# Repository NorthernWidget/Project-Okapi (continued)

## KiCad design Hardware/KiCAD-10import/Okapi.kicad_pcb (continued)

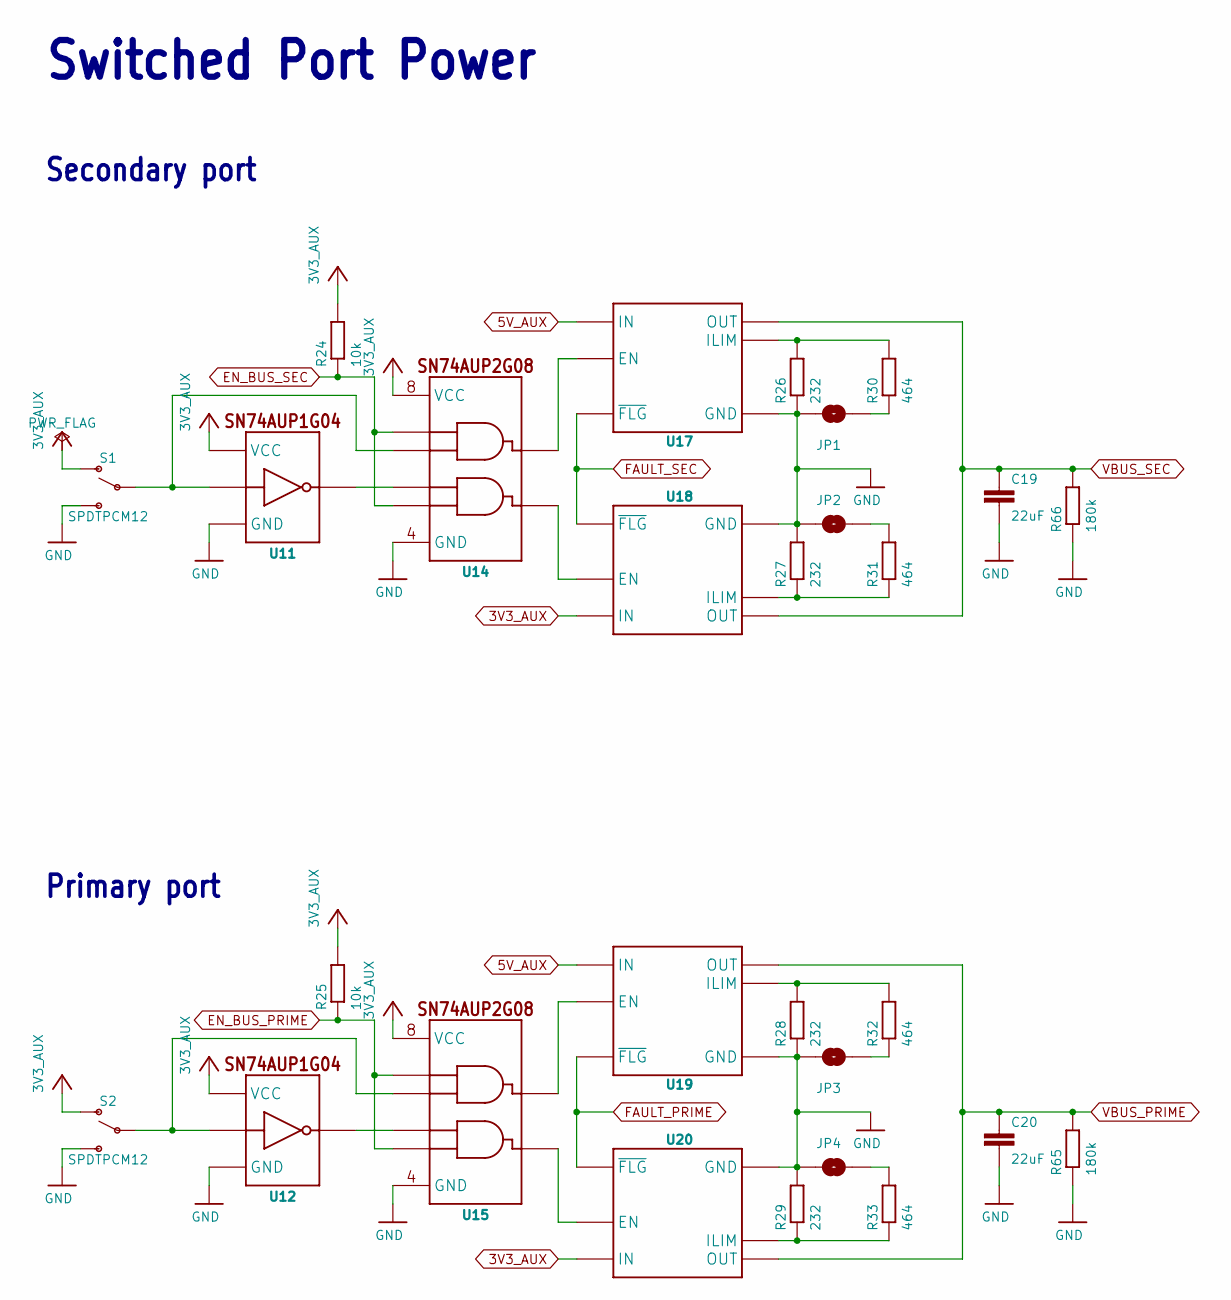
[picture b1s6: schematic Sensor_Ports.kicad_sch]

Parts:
C19, C20: 22uF; C0805; MPN GRM219R61C226ME15L; DIGIKEY 490-9952-1-ND
JP1, JP2, JP3, JP4: JUMPER-SMT_2_NO_SILK; SMT-JUMPER_2_NO_SILK
R24, R25: 10k; R0402; MPN RC0402FR-0710KL; DIGIKEY 311-10.0KLRCT-ND
R26, R27, R28, R29: 232; R0402; MPN RC0402FR-07232RL; DIGIKEY YAG3063CT-ND
R30, R31, R32, R33: 464; R0402; MPN RC0402FR-07464RL; DIGIKEY 311-464LRCT-ND
R65, R66: 180k; R0402; MPN RC0402FR-07180KL; DIGIKEY 311-180KLRCT-ND
S1, S2: SPDTPCM12; PCM12; MPN PCM12SMTR; DIGIKEY 401-2016-1-ND
U11, U12: SN74AUP1G04YFP; DSBGD_4; MPN SN74AUP1G04YFPR; DIGIKEY 296-25196-1-ND
U14, U15: SN74AUP2G08DQE; DQE_R-PX2SON-N8; MPN SN74AUP2G08DQER; DIGIKEY 296-25638-1-ND
U17, U18, U19, U20: MIC2544MSOP; MSOP_8; MPN MIC2544-1YMM; DIGIKEY 576-1738-5-ND

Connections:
3V3_AUX: R24.2, R25.2, S1.1 (O), S2.1 (O), U11.A2 (VCC), U12.A2 (VCC), U14.8 (VCC), U15.8 (VCC), U18.7 (IN), U20.7 (IN); also elsewhere on the board
5V_AUX: U17.7 (IN), U19.7 (IN); also elsewhere on the board
EN_BUS_PRIME: R25.1, U15.1 (A1), U15.6 (B2); also elsewhere on the board
EN_BUS_SEC: R24.1, U14.1 (A1), U14.6 (B2); also elsewhere on the board
FAULT_PRIME: U19.2 (~FLG), U20.2 (~FLG); also elsewhere on the board
FAULT_SEC: U17.2 (~FLG), U18.2 (~FLG); also elsewhere on the board
GND: C19.2, C20.2, JP1.1, JP2.1, JP3.1, JP4.1, R26.1, R27.2, R28.1, R29.2, R65.1, R66.1, S1.3 (S), S2.3 (S), U11.B1 (GND), U12.B1 (GND), U14.4 (GND), U15.4 (GND), U17.3 (GND), U18.3 (GND), U19.3 (GND), U20.3 (GND); also elsewhere on the board
unnamed: JP1.2, R30.1
unnamed: JP2.2, R31.2
unnamed: JP3.2, R32.1
unnamed: JP4.2, R33.2
unnamed: S1.2, U11.A1 (A), U14.2 (B1)
unnamed: S2.2, U12.A1 (A), U15.2 (B1)
unnamed: U11.B2 (Y), U14.5 (A2)
unnamed: U12.B2 (Y), U15.5 (A2)
unnamed: U14.7 (Y1), U17.1 (EN)
unnamed: U14.3 (Y2), U18.1 (EN)
unnamed: U15.7 (Y1), U19.1 (EN)
unnamed: U15.3 (Y2), U20.1 (EN)
unnamed: R26.2, R30.2, U17.5 (ILIM)
unnamed: R27.1, R31.1, U18.5 (ILIM)
unnamed: R28.2, R32.2, U19.5 (ILIM)
unnamed: R29.1, R33.1, U20.5 (ILIM)
VBUS_PRIME: C20.1, R65.2, U19.6 (OUT), U19.8 (OUT), U20.6 (OUT), U20.8 (OUT); also elsewhere on the board
VBUS_SEC: C19.1, R66.2, U17.6 (OUT), U17.8 (OUT), U18.6 (OUT), U18.8 (OUT); also elsewhere on the board

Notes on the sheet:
Primary port
Secondary port
Switched Port Power

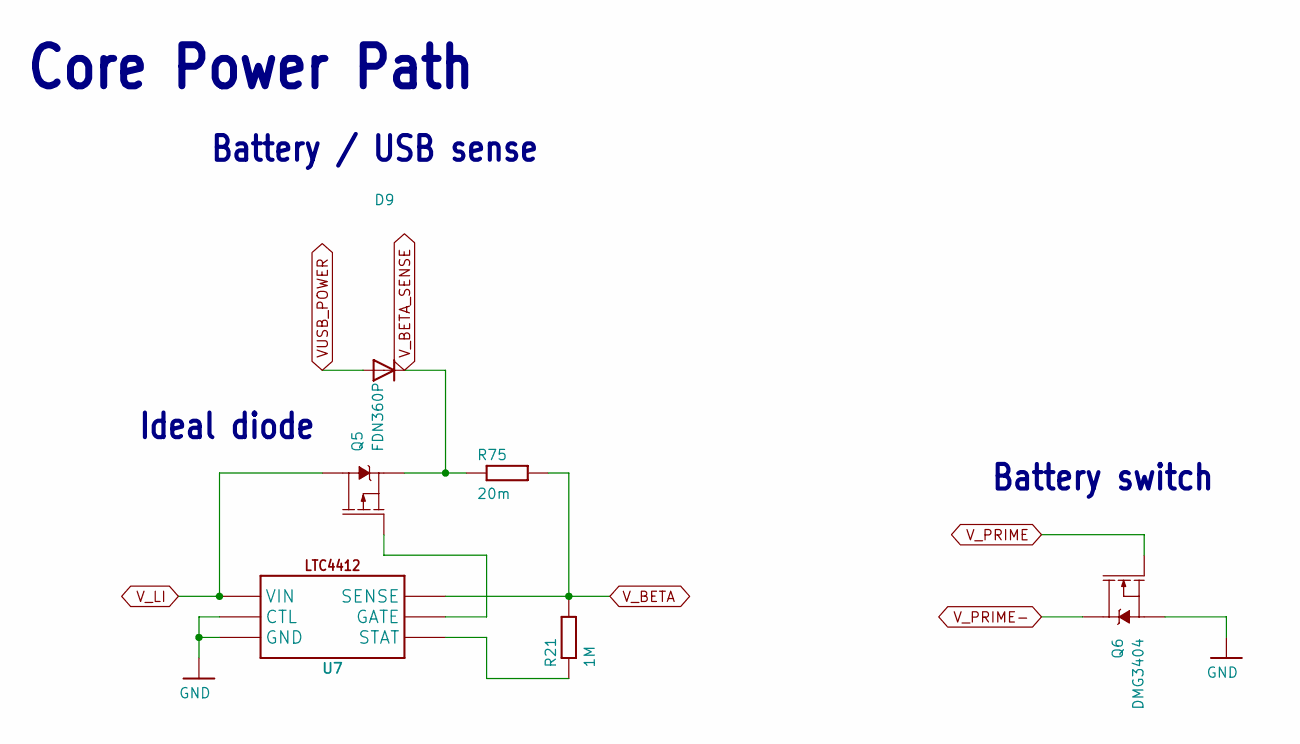
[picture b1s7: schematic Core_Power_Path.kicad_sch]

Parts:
D9: DIODEDO-214AC; DO214AC; MPN B340A-13-F; DIGIKEY B340A-FDICT-ND
Q5: FDN360P; SOT23-3; MPN FDN360P; DIGIKEY FDN360PCT-ND
Q6: DMG3404; SOT23-3; MPN DMG3404L-7; DIGIKEY DMG3404L-7DICT-ND
R21: 1M; R0603; MPN ERJ-3EKF1004V; DIGIKEY P1.00MHCT-ND
R75: 20m; R0805; MPN ERJ-6BWFR020V; DIGIKEY P.02AQCT-ND
U7: LTC4412S6; SOT23-6L; MPN LTC4412ES6#TRPBF; DIGIKEY LTC4412ES6#TRPBFCT-ND

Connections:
GND: Q6.2 (S), U7.2 (GND), U7.3 (CTL); also elsewhere on the board
unnamed: Q5.1 (G), U7.5 (GATE)
unnamed: R21.1, U7.4 (STAT)
VUSB_POWER: D9.A; also elsewhere on the board
V_BETA: R21.2, R75.2, U7.6 (SENSE); also elsewhere on the board
V_BETA_SENSE: D9.C, Q5.2 (S), R75.1; also elsewhere on the board
V_LI: Q5.3 (D), U7.1 (VIN); also elsewhere on the board
V_PRIME: Q6.1 (G); also elsewhere on the board
V_PRIME-: Q6.3 (D); also elsewhere on the board

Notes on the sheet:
Core Power Path
Battery switch
Ideal diode
Battery / USB sense

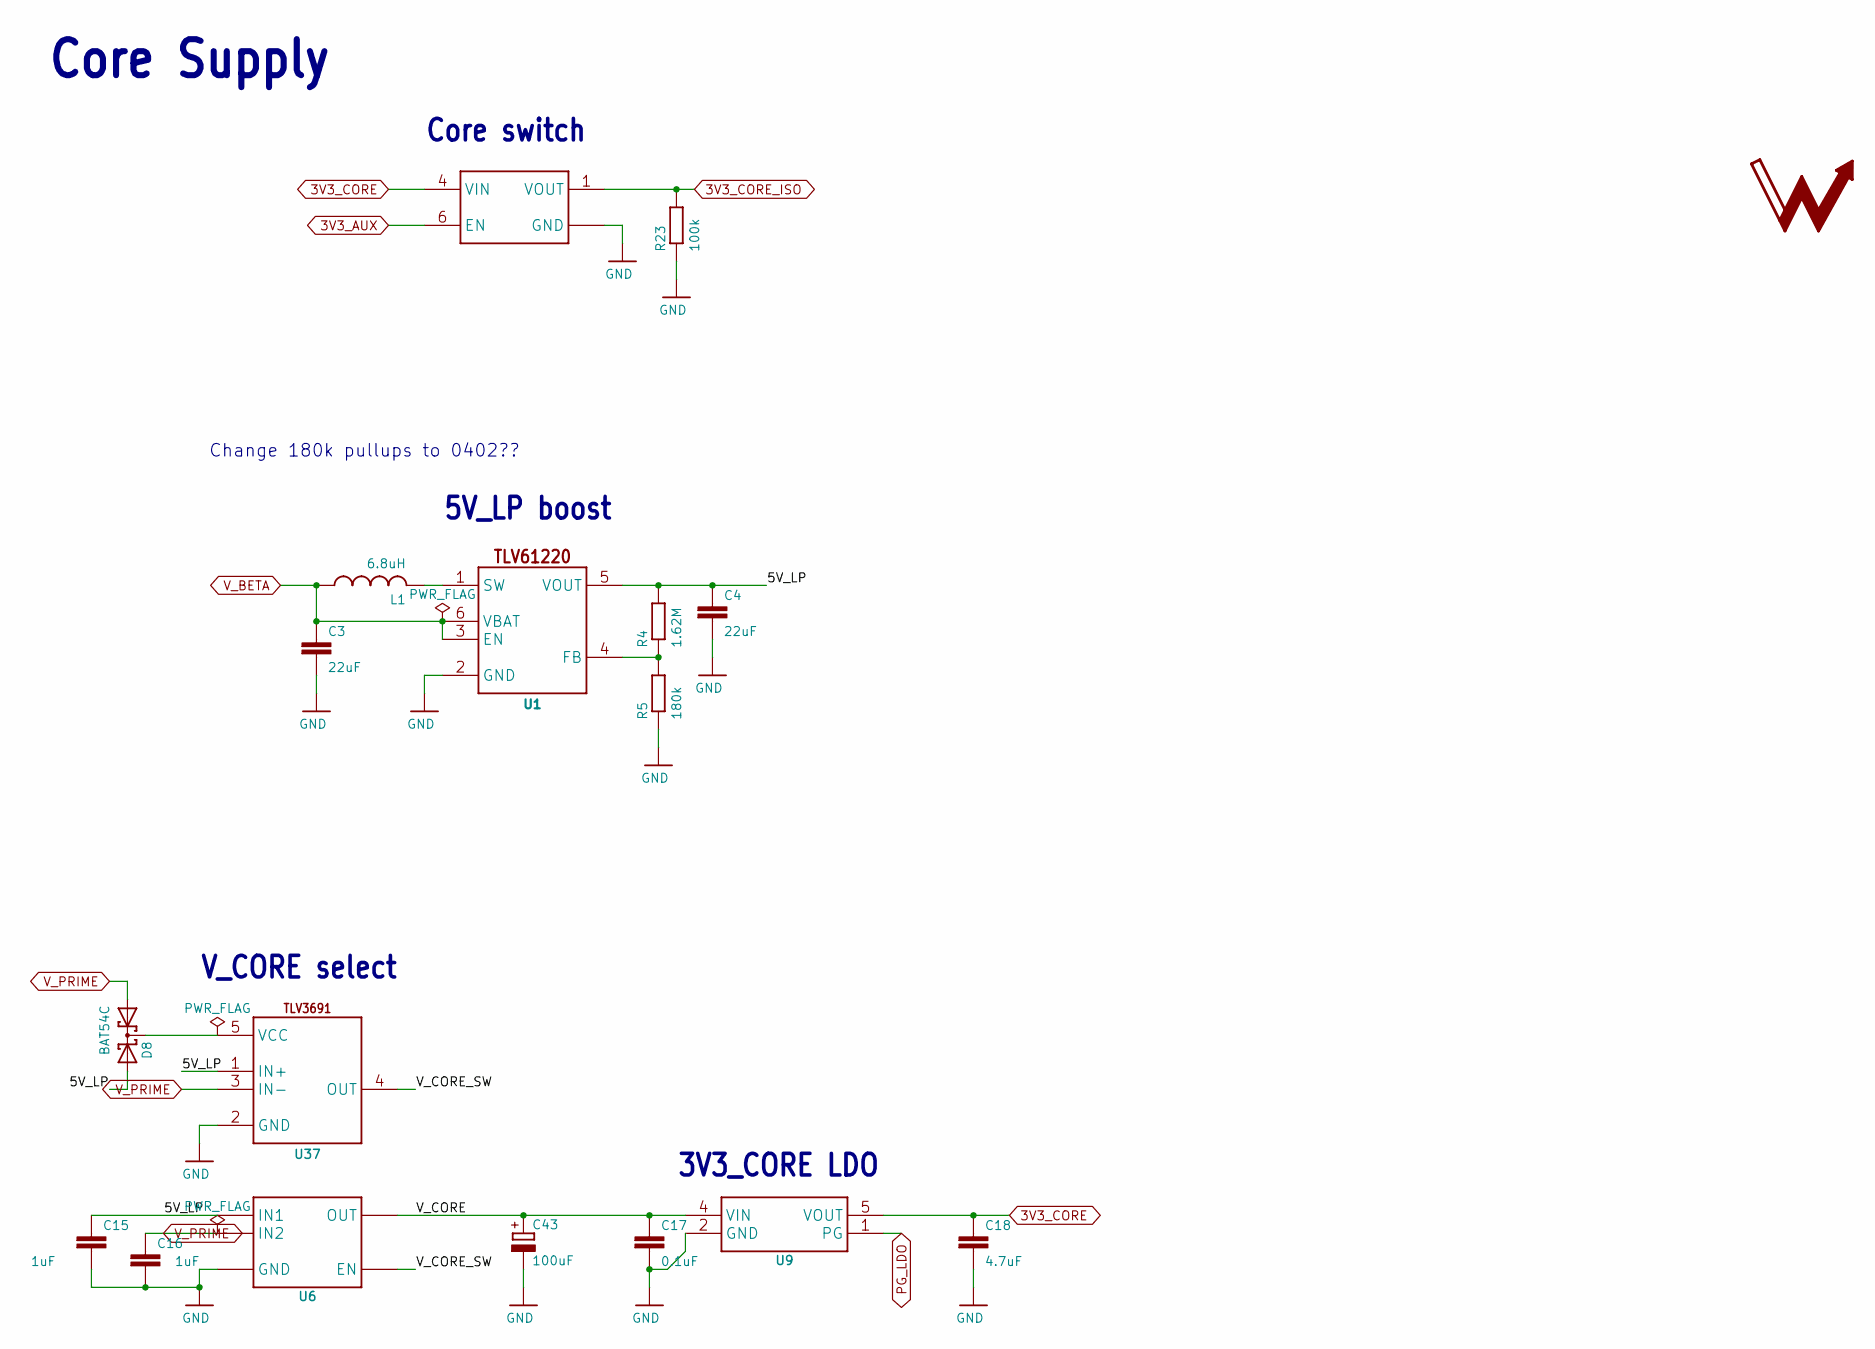
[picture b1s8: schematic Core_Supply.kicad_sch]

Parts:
C3, C4: 22uF; C0805; MPN GRM219R61C226ME15L; DIGIKEY 490-9952-1-ND
C15, C16: 1uF; C0402; MPN CL05A105KA5NQNC; DIGIKEY 1276-1445-1-ND
C17: 0.1uF; C0402; MPN GCM155R71C104KA55D; DIGIKEY 490-4759-1-ND
C18: 4.7uF; C0603; MPN GRM188Z71C475KE21D; DIGIKEY 490-GRM188Z71C475KE21DCT-ND
C43: 100uF; C1206_TANT; MPN GRM31CR61A107MEA8L; DIGIKEY 490-GRM31CR61A107MEA8LCT-ND
D8: BAT54C; SOT23-3; MPN BAT54CLT1G; DIGIKEY BAT54CLT1GOSCT-ND
L1: 6.8uH; 1008; MPN 74438323068; DIGIKEY 732-4849-1-ND
LOGO1: NWLOGO_MED
R4: 1.62M; R0603; MPN CRCW06031M62FKEA; DIGIKEY 541-1.62MHCT-ND
R5: 180k; R0402; MPN RC0402FR-07180KL; DIGIKEY 311-180KLRCT-ND
R23: 100k; R0402; MPN RC0402FR-07100KL; DIGIKEY 311-100KLRCT-ND
U1: TLV61220DBV; DBV_R-PDSO-G6; MPN TLV61220DBVR; DIGIKEY 296-30547-1-ND
U6: TPS2105; SOT23-5; MPN TPS2105DBVR; DIGIKEY 296-10883-1-ND
U9: TPS797; DCK_R-PDSO-G5; MPN TPS79733DCKR; DIGIKEY 296-11990-1-ND
U37: TLV3691DCK; DCK_R-PDSO-G5; MPN TLV3691IDCKR; DIGIKEY 296-37910-1-ND
U39: MIC94094C6; SC-70_6; MPN MIC94094YC6-TR; DIGIKEY 576-3492-1-ND

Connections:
3V3_AUX: U39.6 (EN); also elsewhere on the board
3V3_CORE: C18.1, U9.5 (VOUT), U39.4 (VIN); also elsewhere on the board
3V3_CORE_ISO: R23.2, U39.1 (VOUT); also elsewhere on the board
/Core_Supply/5V_LP: C4.1, C15.1, D8.2 (A2), R4.2, U1.5 (VOUT), U6.5 (IN1), U37.1 (IN+)
/Core_Supply/V_CORE: C17.1, C43.+, U6.4 (OUT), U9.4 (VIN)
/Core_Supply/V_CORE_SW: U6.1 (EN), U37.4 (OUT)
GND: C3.2, C4.2, C15.2, C16.2, C17.2, C18.2, C43.-, R5.1, R23.1, U1.2 (GND), U6.2 (GND), U9.2 (GND), U37.2 (GND), U39.2 (GND), U39.5 (GND); also elsewhere on the board
unnamed: D8.3 (C), U37.5 (VCC)
unnamed: R4.1, R5.2, U1.4 (FB)
unnamed: L1.2, U1.1 (SW)
PG_LDO: U9.1 (PG); also elsewhere on the board
V_BETA: C3.1, L1.1, U1.3 (EN), U1.6 (VBAT); also elsewhere on the board
V_PRIME: C16.1, D8.1 (A1), U6.3 (IN2), U37.3 (IN-); also elsewhere on the board

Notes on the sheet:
5V_LP boost
Core switch
Core Supply
3V3_CORE LDO
V_CORE select
Change 180k pullups to 0402??

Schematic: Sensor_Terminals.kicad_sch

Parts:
J1, J4: CONN_82.54_SCREW; 1X08_SCREW; MPN OSTVN08A150; DIGIKEY ED10566-ND
J2: CONN_102.54_SCREW; 1X10_SCREW; MPN OSTVN10A150; DIGIKEY ED10567-ND
J3: CONN_42.54_SCREW; 1X04_SCREW; MPN OSTVN04A150; DIGIKEY ED10563-ND

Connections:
ADC_0: J1.8; also elsewhere on the board
ADC_1: J2.1; also elsewhere on the board
ADC_2: J4.5; also elsewhere on the board
ADC_3: J4.6; also elsewhere on the board
CS_OUT: J2.6; also elsewhere on the board
DAC_OUT: J1.7; also elsewhere on the board
GND: J1.1, J2.10, J3.1, J4.1; also elsewhere on the board
GPIO_0_OUT: J1.6; also elsewhere on the board
GPIO_1_OUT: J1.5; also elsewhere on the board
GPIO_2_OUT: J4.7; also elsewhere on the board
GPIO_3_OUT: J4.8; also elsewhere on the board
MISO_OUT: J2.5; also elsewhere on the board
MOSI_OUT: J2.4; also elsewhere on the board
RX_OUT_PRIME: J1.3; also elsewhere on the board
RX_OUT_SEC: J3.3; also elsewhere on the board
SCK_OUT: J2.3; also elsewhere on the board
SCL_OUT_PRIME: J2.7; also elsewhere on the board
SCL_OUT_SEC: J4.4; also elsewhere on the board
SDA_OUT_PRIME: J2.8; also elsewhere on the board
SDA_OUT_SEC: J4.3; also elsewhere on the board
TX_OUT_PRIME: J1.4; also elsewhere on the board
TX_OUT_SEC: J3.4; also elsewhere on the board
VBUS_PRIME: J1.2, J2.9; also elsewhere on the board
VBUS_SEC: J3.2, J4.2; also elsewhere on the board
VREF: J2.2; also elsewhere on the board

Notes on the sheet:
Sensor Terminals

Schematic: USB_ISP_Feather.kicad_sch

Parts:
C21, C25: 0.1uF; C0402; MPN GCM155R71C104KA55D; DIGIKEY 490-4759-1-ND
C22: 4.7uF; C0603; MPN GRM188Z71C475KE21D; DIGIKEY 490-GRM188Z71C475KE21DCT-ND
C23, C24: 12pF; C0402; MPN CGA2B2C0G1H120J050BA; DIGIKEY 445-5585-1-ND
D4: CLVBA-FKA; MPN CLVBA-FKA-CAEDH8BBB7A363; DIGIKEY CLVBA-FKA-CAEDH8BBB7A363CT-ND
F1: PPTC1.5A; 1206; MPN MF-NSMF150-2; DIGIKEY MF-NSMF150-2CT-ND
H1, H2, H3: MOUNTING_HOLE4_NP; 4_40; MPN DNP; DIGIKEY DNP
J10: USB_C; USB_C_CUSB31-CFM2AX-01-X; MPN USB4105-GF-A; DIGIKEY 2073-USB4105-GF-ACT-ND
R34, R35: 27; R0402; MPN RC0402FR-0727RL; DIGIKEY YAG3086CT-ND
R36, R37, R38, R39, R40: 330; R0402; MPN RC0402FR-07330RL; DIGIKEY 311-330LRCT-ND
R63: 100k; R0402; MPN RC0402FR-07100KL; DIGIKEY 311-100KLRCT-ND
R84, R85: 5.1k; R0402; MPN RC0402FR-075K1L; DIGIKEY 311-5.10KLRCT-ND
U23: FT231X-Q; QFN20; MPN FT231XQ-R; DIGIKEY 768-1128-1-ND

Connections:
3V3_CORE: D4.2 (ANODE); also elsewhere on the board
/USB_ISP_Feather/3V3_FTDI: C25.1, U23.10 (3V3OUT), U23.11 (RESET#), U23.20 (VCCIO)
/USB_ISP_Feather/CC1: J10.A5 (CC1), R85.2
/USB_ISP_Feather/CC2: J10.B5 (CC2), R84.2
/USB_ISP_Feather/D+: C24.2, J10.A6 (D+), J10.B6 (D+), R35.2
/USB_ISP_Feather/D-: C23.2, J10.A7 (D-), J10.B7 (D-), R34.2
/USB_ISP_Feather/VUSB: C21.1, C22.1, F1.1, J10.A4B9 (VBUS), J10.B4A9 (VBUS), U23.12 (VCC)
ALIVE_LED: R37.2; also elsewhere on the board
DTR: U23.18 (DTR#); also elsewhere on the board
GND: C21.2, C22.2, C23.1, C24.1, C25.2, J10.A1B12 (GND), J10.B1A12 (GND), J10.S1 (SHIELD), R63.1, R84.1, R85.1, U23.3 (GND), U23.6 (CTS#), U23.13 (GND), U23.EP (GND); also elsewhere on the board
unnamed: D4.3 (BLUE_CATH), R36.1
unnamed: D4.4 (GREEN_CATH), R37.1
unnamed: D4.1 (RED_CATH), R39.1
unnamed: R39.2, U23.14 (CBUS1)
unnamed: R36.2, U23.7 (CBUS2)
unnamed: R40.2, U23.1 (RXD)
unnamed: R38.2, U23.17 (TXD)
unnamed: R34.1, U23.9 (USBDM)
unnamed: R35.1, U23.8 (USBDP)
RX: R38.1; also elsewhere on the board
TX: R40.1; also elsewhere on the board
VUSB_POWER: F1.2, R63.2; also elsewhere on the board

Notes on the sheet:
FT231X USB serial
USB-C
USB

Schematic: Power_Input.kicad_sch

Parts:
C10, C14: 22uF; C0805; MPN GRM219R61C226ME15L; DIGIKEY 490-9952-1-ND
C11, C13: 1uF; C0603; MPN TMK107B7105KA-T; DIGIKEY 587-2984-1-ND
C12: 0.1uF; C0402; MPN GCM155R71C104KA55D; DIGIKEY 490-4759-1-ND
D1, D3: DIODEDO-214AC; DO214AC; MPN CMSH3-40MA TR13; DIGIKEY CMSH3-40MATR13CT-ND
D2: DIODESOD-323; SOD323-R; MPN CMDSH2-3 TR; DIGIKEY CMDSH2-3CT-ND
J5, J6, J7: CONN_022.54_SCREW; 1X02_2.54_SCREWTERM; MPN OSTVN02A150; DIGIKEY ED10561-ND
J8: JST_2MM_MALE; JST-2-SMD; MPN S2B-PH-SM4-TB(LF)(SN); DIGIKEY 455-1749-1-ND
L4: 4.7uH; WE-MAIA(4.1X4.1); MPN 78438356047; DIGIKEY 732-11316-1-ND
Q1, Q2: DMG3404; SOT23-3; MPN DMG3404L-7; DIGIKEY DMG3404L-7DICT-ND
Q8: 2N7002; SOT323; MPN 2N7002WT1G; DIGIKEY 2N7002WT1GOSCT-ND
R9: 220R; R0402; MPN CRGCQ0402F220R; DIGIKEY A129619CT-ND
R10: 3m; R0805; MPN PMR10EZPFV3L00; DIGIKEY RHM.003AJCT-ND
R11: 27; R0402; MPN RC0402FR-0727RL; DIGIKEY YAG3086CT-ND
R12, R15: 1k; R0402; MPN RC0402FR-071KL; DIGIKEY 311-1.00KLRCT-ND
R13: 180k; R0603; MPN ERJ-3EKF1803V; DIGIKEY P180KHCT-ND
R14: 100R; R0402; MPN RC0402FR-07100RL; DIGIKEY 311-100LRCT-ND
R16: 91k; R0603; MPN ERJ-3EKF9102V; DIGIKEY P91.0KHCT-ND
R17: 330k; R0603; MPN ERJ-3EKF3303V; DIGIKEY P330KHCT-ND
R22: 143k; R0402_0603; MPN RC0603FR-07143KL; DIGIKEY 311-143KHRCT-ND
R69: 100k; R0402_0603; MPN RC0402FR-07100KL; DIGIKEY 311-100KLRCT-ND
R70: 200k; R0402_0603; MPN ERJ-2RKF2003X; DIGIKEY P200KLCT-ND
R71: 1M; R0402_0603; MPN RC0402FR-071ML; DIGIKEY 311-1.00MLRCT-ND
R72, R73: 20m; R0805; MPN ERJ-6BWFR020V; DIGIKEY P.02AQCT-ND
R74: 50m; R0805; MPN ERJ-6BWFR050V; DIGIKEY P17581CT-ND
S5: BUTTON2.6X1.6; SWITCH_2.6X1.6; MPN EVP-BB2A9B000; DIGIKEY P19888CT-ND
U4: LT3652DD; DFN_12_3X3; MPN LT3652EDD#PBF; DIGIKEY LT3652EDD#PBF-ND
U5: BQ2980RUG; RUG_S-PQFP-N8; MPN BQ298000RUGT; DIGIKEY 296-47578-1-ND

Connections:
/Power_Input/MPPT_SHDN: R70.2, R71.1, U4.3 (~SHDN)
/Power_Input/MPPT_VIN_REG: R22.1, R69.2, U4.2 (VIN_REG)
BMS_CTR: R14.1; also elsewhere on the board
GND: C10.2, C12.2, C14.2, D3.A, J7.P1 (1), Q8.2 (S), R10.2, R12.1, R17.2, R69.1, U4.6 (TIMER), U4.EP (GND_PAD), U5.4 (CS); also elsewhere on the board
LI+: J6.P2 (2), J8.2 (+), Q1.2 (S), R9.2, R11.2, S5.A (1), S5.A' (2)
LI-: C11.2, J6.P1 (1), J8.1 (-), R10.1, U5.3 (VSS)
MPPT_CHRG: Q8.1 (G), U4.4 (~CHRG); also elsewhere on the board
MPPT_FAULT: U4.5 (~FAULT); also elsewhere on the board
unnamed: C13.1, D3.C, L4.P$1 (1), U4.12 (SW)
unnamed: Q1.3 (D), Q2.3 (D)
unnamed: Q1.1 (G), U5.8 (CHG)
unnamed: Q2.1 (G), U5.7 (DSG)
unnamed: Q8.3 (D), R70.1
unnamed: R13.1, R16.2, R17.1
unnamed: C13.2, D2.C, U4.11 (BOOST)
unnamed: R13.2, U4.7 (VFB)
unnamed: R11.1, U5.1 (BAT)
unnamed: C12.1, R12.2, R14.2, U5.5 (CTR)
unnamed: R15.2, U5.6 (PACK)
unnamed: C11.1, R9.1, U5.2 (VDD)
V_LI: C14.1, D2.A, L4.P$2 (2), R15.1, R16.1, R72.2, S5.B (3), S5.B' (4), U4.9 (BAT), U4.10 (SENSE); also elsewhere on the board
V_LI_SENSE: Q2.2 (S), R72.1; also elsewhere on the board
V_PRIME: R73.2; also elsewhere on the board
V_PRIME-: J5.P1 (1); also elsewhere on the board
V_PRIME_SENSE: J5.P2 (2), R73.1; also elsewhere on the board
V_SOLAR: D1.A, J7.P2 (2)
V_SOLAR_IN: C10.1, R22.2, R71.2, R74.2, U4.1 (VIN); also elsewhere on the board
V_SOLAR_SENSE: D1.C, R74.1; also elsewhere on the board

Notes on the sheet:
V_PRIME
Solar
Battery protection
Solar charger
Battery
Reverse Polarity Protection
Terminals
Battery Protection & Solar Charger
Manual start switch

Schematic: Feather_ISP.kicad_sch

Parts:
ISP1: AVRISP-6; AVRISP; MPN 67997-206HLF; DIGIKEY 609-3234-ND
JP5: JUMPER-SMT_2_NO_SILK; SMT-JUMPER_2_NO_SILK
MS1: FEATHERWINGLAYOUT; FEATHERWING_MIN
Q3: FDN360P; SOT23-3; MPN FDN360P; DIGIKEY FDN360PCT-ND
Q4: 2N7002; SOT323; MPN 2N7002WT1G; DIGIKEY 2N7002WT1GOSCT-ND
R19: 100k; R0402; MPN RC0402FR-07100KL; DIGIKEY 311-100KLRCT-ND
R20: 130k; R0603; MPN ERJ-3EKF1303V; DIGIKEY P130KHCT-ND
R54: 10k; R0402; MPN RC0402FR-0710KL; DIGIKEY 311-10.0KLRCT-ND
U8: TPL5111DDC; DDC_R-PDSO-G6; MPN TPL5111DDCR; DIGIKEY 296-46226-1-ND
U10: TPS22917DBV; DBV_R-PDSO-G6; MPN TPS22917DBVT; DIGIKEY 296-48370-1-ND

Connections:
3V3_CORE: ISP1.2 (VCC), Q3.2 (S), R19.2, U8.1 (VDD), U8.6 (EN); also elsewhere on the board
5V_AUX: MS1.26 (USB); also elsewhere on the board
GND: ISP1.6 (GND), MS1.4 (GND), Q4.2 (S), R20.1, R54.1, U8.2 (GND), U10.2 (GND); also elsewhere on the board
MISO: ISP1.1 (MISO), MS1.13 (GPIOMISO); also elsewhere on the board
MOSI: ISP1.4 (MOSI); also elsewhere on the board
MOSI_BUF: MS1.12 (GPIOMOSI); also elsewhere on the board
unnamed: Q3.3 (D), R20.2, U8.3 (DELAY)
unnamed: U8.5 (DRVN), U10.3 (ON)
PARTICLE_3V3: MS1.2 (3V); also elsewhere on the board
PARTICLE_CTS: MS1.20 (GPIO6); also elsewhere on the board
PARTICLE_EN: Q3.1 (G), R19.1; also elsewhere on the board
PARTICLE_GPIO: MS1.10 (GPIOA5); also elsewhere on the board
PARTICLE_RTS: MS1.19 (GPIO5); also elsewhere on the board
PARTICLE_VCC: MS1.28 (VBAT), U10.5 (QOD), U10.6 (VOUT); also elsewhere on the board
RST: ISP1.5 (RST), Q4.3 (D); also elsewhere on the board
RST_TRIG: MS1.21 (GPIO9), Q4.1 (G), R54.2; also elsewhere on the board
RX: MS1.15 (GPIOTX); also elsewhere on the board
SCK: ISP1.3 (SCK); also elsewhere on the board
SCK_BUF: MS1.11 (GPIOSCK); also elsewhere on the board
SCL_PARTICLE: MS1.18 (GPIOSCL); also elsewhere on the board
SDA_EXT: JP5.2; also elsewhere on the board
SDA_OB: JP5.1; also elsewhere on the board
SDA_PARTICLE: MS1.17 (GPIOSDA); also elsewhere on the board
TX: MS1.14 (GPIORX); also elsewhere on the board
V_LI: U10.1 (VIN); also elsewhere on the board
WD_DONE: MS1.8 (GPIOA3), U8.4 (DONE); also elsewhere on the board

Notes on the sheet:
SDA jumper
ICSP header
Jump SDA channels together, prevents using occupied addresses on the external I2C port
Feather Power Timer
ISP & Feather
Feather socket
ICSP
Feather enable

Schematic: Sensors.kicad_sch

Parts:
C38, C46, C47, C48, C57: 0.1uF; C0402; MPN GCM155R71C104KA55D; DIGIKEY 490-4759-1-ND
U31: BME280; MPN BME280; DIGIKEY 828-1063-1-ND
U38: MLX90393; QFN16_3X3; MPN MLX90393SLW-ABA-011-RE; DIGIKEY MLX90393SLW-ABA-011-RECT-ND
U43: BMA456; LGA-12_2X2; MPN BMA456; DIGIKEY 828-1075-1-ND
U44: VEML6030; MPN VEML6030-GS15; DIGIKEY VEML6030-GS15CT-ND

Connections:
3V3_AUX: C38.1, C46.1, C47.1, C48.1, C57.1, U31.2 (CSB), U31.5 (SDO), U31.6 (VDDIO), U31.8 (VDD), U38.2 (MS/CS), U38.8 (VDD_IO), U38.15 (VDD), U43.3 (VCC), U43.7 (VCC), U43.10 (CSB), U44.4 (ADDR), U44.6 (VDD); also elsewhere on the board
GND: C38.2, C46.2, C47.2, C48.2, C57.2, U31.1 (GND), U31.7 (GND), U38.4 (NC), U38.9 (NC), U38.10 (NC), U38.11 (A1), U38.12 (A0), U38.13 (VSS), U38.14 (NC), U38.16 (NC), U38.EP (VSS), U43.1 (SDO), U43.8 (GND), U43.9 (GND), U44.1 (GND); also elsewhere on the board
SCL: U31.4 (SCK), U38.3 (SCL/SCLK), U43.12 (SCL), U44.5 (SCL); also elsewhere on the board
SDA_OB: U31.3 (SDI), U38.5 (SDA/MOSI), U43.2 (SDA), U44.2 (SDA); also elsewhere on the board

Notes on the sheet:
BMA456 accelerometer
VEML6030 light
ADR=0x77
On-Board Sensors
ADR = 0x48
MLX90393 magnetometer
BME280 environment
ADR=0x18
ADR=0x0C

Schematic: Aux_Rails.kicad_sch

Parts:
C1: 4.7uF; C0603; MPN GRM188Z71C475KE21D; DIGIKEY 490-GRM188Z71C475KE21DCT-ND
C2, C7, C8, C9: 22uF; C0805; MPN GRM219R61C226ME15L; DIGIKEY 490-9952-1-ND
C5: 220uF; C2917; MPN TPSY227K010R0100; DIGIKEY 478-5408-1-ND
C6: 68pF; C0402; MPN 885012005060; DIGIKEY 732-7474-1-ND
L2: 10uH; WE-XHMI(6.65X6.45); MPN 74439346100; DIGIKEY 732-10707-1-ND
L3: 1uH; WE-LQS(3X3); MPN 74404032010; DIGIKEY 732-5491-1-ND
Q7: 2N7002; SOT323; MPN 2N7002WT1G; DIGIKEY 2N7002WT1GOSCT-ND
R1, R7, R8: 180k; R0402; MPN RC0402FR-07180KL; DIGIKEY 311-180KLRCT-ND
R2: 1.62M; R0603; MPN CRCW06031M62FKEA; DIGIKEY 541-1.62MHCT-ND
R3: 330k; R0603; MPN ERJ-3EKF3303V; DIGIKEY P330KHCT-ND
R6: 820k; R0603; MPN RC0603FR-07820KL; DIGIKEY 311-820KHRCT-ND
R67: 10k; R0402; MPN RC0402FR-0710KL; DIGIKEY 311-10.0KLRCT-ND
U2: TPS6282DLC; DLC_8; MPN TPS62822DLCT; DIGIKEY 296-49512-1-ND
U3: TPS61032RSA; RSA_S-PVQFN-N16; MPN TPS61032RSAR; DIGIKEY 296-16662-1-ND
U13: SN74AUP1G04YFP; DSBGD_4; MPN SN74AUP1G04YFPR; DIGIKEY 296-25196-1-ND
U16: SN74AUP2G08DQE; DQE_R-PX2SON-N8; MPN SN74AUP2G08DQER; DIGIKEY 296-25638-1-ND
U21, U22: TPS22917DBV; DBV_R-PDSO-G6; MPN TPS22917DBVT; DIGIKEY 296-48370-1-ND
U40: SN74AHC1G86DCK; DCK_R-PDSO-G5; MPN SN74AHC1G86DCKR; DIGIKEY 296-8750-1-ND
U$1, U$2: VDIV-JP; VDIV_GENERIC

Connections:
3V3_AUX: C6.1, C8.1, C9.1, L3.P$2 (2), R6.2; also elsewhere on the board
3V3_AUX_PG: R1.1, U2.8 (PG); also elsewhere on the board
3V3_CORE: U13.A2 (VCC), U16.8 (VCC), U40.5 (VCC); also elsewhere on the board
5V_AUX: C1.1, C5.+, C7.1, Q7.3 (D), R1.2, R8.2, R67.2, U2.7 (VIN), U3.1 (VOUT), U3.15 (VOUT), U3.16 (VOUT); also elsewhere on the board
C0: U16.2 (B1), U40.1 (A); also elsewhere on the board
C1: U16.6 (B2), U40.2 (B); also elsewhere on the board
GND: C1.2, C2.2, C5.-, C7.2, C8.2, C9.2, Q7.2 (S), R3.1, R7.1, R67.1, U2.3 (AGND), U2.5 (PGND), U3.5 (PGND), U3.6 (PGND), U3.7 (PGND), U3.13 (GND), U3.PAD (PGND), U3.PAD@1 (PGND), U3.PAD@2 (PGND), U3.PAD@3 (PGND), U3.PAD@4 (PGND), U3.PAD@5 (PGND), U3.PAD@6 (PGND), U3.PAD@7 (PGND), U3.PAD@8 (PGND), U3.PAD@9 (PGND), U13.B1 (GND), U16.4 (GND), U21.2 (GND), U22.2 (GND), U40.3 (GND); also elsewhere on the board
LBI: R8.1, U3.12 (LBO); also elsewhere on the board
unnamed: L2.2, U3.3 (SW), U3.4 (SW)
unnamed: L3.P$1 (1), U2.6 (SW)
unnamed: Q7.1 (G), U13.B2 (Y)
unnamed: C6.2, R6.1, R7.2, U2.2 (FB)
unnamed: R2.1, R3.2, U3.9 (LBI)
unnamed: U16.7 (Y1), U21.3 (ON)
unnamed: U16.3 (Y2), U22.3 (ON)
POWER_EN: U2.1 (EN), U3.11 (EN), U13.A1 (A), U16.1 (A1), U16.5 (A2), U40.4 (Y)
V_BETA: U22.1 (VIN); also elsewhere on the board
V_HP: C2.1, L2.1, R2.2, U3.8 (VBAT), U21.6 (VOUT), U22.6 (VOUT)
V_HP_SYNC: U3.10 (SYNC); also elsewhere on the board
V_PRIME: U21.1 (VIN); also elsewhere on the board

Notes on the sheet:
Remove LBI pullup??
3V3_AUX & 5V_AUX Rails
POWER_EN logic
C0/C1 decode
Remove PG pullup?
V_HP switches
3V3_AUX buck
V_HP Source Select
5V_AUX boost

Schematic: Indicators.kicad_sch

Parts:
D5: CLVBA-FKA; MPN CLVBA-FKA-CAEDH8BBB7A363; DIGIKEY CLVBA-FKA-CAEDH8BBB7A363CT-ND
D10, D13, D16: LEDGREEN0603; LED_0603; MPN 150060GS75000; DIGIKEY 732-4971-1-ND
D11, D14, D17: LEDYELLOW0603; LED_0603; MPN 150060YS75000; DIGIKEY 732-4981-1-ND
D12, D18: LEDRED0603; LED_0603; MPN 150060RS75000; DIGIKEY 732-4978-1-ND
R18: 100k; R0402; MPN RC0402FR-07100KL; DIGIKEY 311-100KLRCT-ND
R42, R43, R44: 330; R0402; MPN RC0402FR-07330RL; DIGIKEY 311-330LRCT-ND
R45: 10k; R0402; MPN RC0402FR-0710KL; DIGIKEY 311-10.0KLRCT-ND
R53, R60, R64, R76, R77, R78, R79, R80: 220R; R0402; MPN CRGCQ0402F220R; DIGIKEY A129619CT-ND
S3: BUTTON4.2X3.2; SWITCH_4.2X3.2; MPN PTS810 SJG 250 SMTR LFS; DIGIKEY CKN10504CT-ND
U45: PCA9634QFN; QFN20_5X5; MPN PCA9634BS,118; DIGIKEY 568-8717-1-ND

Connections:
3V3_CORE: D5.2 (ANODE), R18.2, R45.2, R53.2, R60.2, R64.2, R76.2, R77.2, R78.2, R79.2, R80.2, U45.3 (A4), U45.15 (A6), U45.18 (VDD), U45.20 (A1); also elsewhere on the board
GND: S3.1, S3.2, U45.1 (A2), U45.2 (A3), U45.8 (VSS), U45.14 (A5), U45.19 (A0), U45.EP (VSS); also elsewhere on the board
LED1: R44.1; also elsewhere on the board
LED2: R42.1; also elsewhere on the board
LED3: R43.1; also elsewhere on the board
LOG_INT: R45.1, S3.3 (4), S3.4 (3); also elsewhere on the board
unnamed: D5.3 (BLUE_CATH), R42.2
unnamed: D5.4 (GREEN_CATH), R43.2
unnamed: D5.1 (RED_CATH), R44.2
unnamed: D10.ANODE, R53.1
unnamed: D11.ANODE, R60.1
unnamed: D12.ANODE, R64.1
unnamed: D13.ANODE, R76.1
unnamed: D14.ANODE, R77.1
unnamed: D16.ANODE, R78.1
unnamed: D17.ANODE, R79.1
unnamed: D18.ANODE, R80.1
unnamed: D10.CATHODE, U45.4 (LED0)
unnamed: D11.CATHODE, U45.5 (LED1)
unnamed: D12.CATHODE, U45.6 (LED2)
unnamed: D13.CATHODE, U45.7 (LED3)
unnamed: D14.CATHODE, U45.9 (LED4)
unnamed: D16.CATHODE, U45.10 (LED5)
unnamed: D17.CATHODE, U45.11 (LED6)
unnamed: D18.CATHODE, U45.12 (LED7)
SCL: U45.16 (SCL); also elsewhere on the board
SDA_OB: U45.17 (SDA); also elsewhere on the board
~LED_EN: R18.1, U45.13 (~OE); also elsewhere on the board

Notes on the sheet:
Log button
PCA9634 LED driver
Status LED
ADR: 0x52
Status LED & Log Button
Indicator LEDs
Select address~{}

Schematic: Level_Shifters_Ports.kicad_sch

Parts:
C26, C27, C28, C44, C45: 0.1uF; C0402; MPN GCM155R71C104KA55D; DIGIKEY 490-4759-1-ND
R46, R47: 10k; R0402; MPN RC0402FR-0710KL; DIGIKEY 311-10.0KLRCT-ND
U27, U29, U42: TXS0104RGY; RGY_S-PVQFN-N14; MPN TXS0104ERGYR; DIGIKEY 296-20698-1-ND
U28, U36: TCA9406DCU; DCU_(R-PDSO-G8); MPN TCA9406DCUR; DIGIKEY 296-28109-1-ND

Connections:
3V3_CORE_ISO: C26.1, C27.1, C28.1, C44.1, C45.1, R46.2, R47.2, U27.1 (VA), U28.3 (VCCA), U29.1 (VA), U36.3 (VCCA), U42.1 (VA); also elsewhere on the board
BUS_LOGIC_EN_PRIME: R46.1, U27.8 (EN), U28.6 (OE), U29.8 (EN); also elsewhere on the board
BUS_LOGIC_EN_SEC: R47.1, U36.6 (OE), U42.8 (EN); also elsewhere on the board
CS_EXT: U27.2 (A1); also elsewhere on the board
CS_OUT: U27.13 (B1); also elsewhere on the board
GND: C26.2, C27.2, C28.2, C44.2, C45.2, U27.7 (GND), U27.EP (GND), U28.2 (GND), U29.7 (GND), U29.EP (GND), U36.2 (GND), U42.7 (GND), U42.EP (GND); also elsewhere on the board
GPIO_0: U29.2 (A1); also elsewhere on the board
GPIO_0_OUT: U29.13 (B1); also elsewhere on the board
GPIO_1: U29.3 (A2); also elsewhere on the board
GPIO_1_OUT: U29.12 (B2); also elsewhere on the board
GPIO_2: U42.5 (A4); also elsewhere on the board
GPIO_2_OUT: U42.10 (B4); also elsewhere on the board
GPIO_3: U42.4 (A3); also elsewhere on the board
GPIO_3_OUT: U42.11 (B3); also elsewhere on the board
MISO: U27.3 (A2); also elsewhere on the board
MISO_OUT: U27.12 (B2); also elsewhere on the board
MOSI: U27.4 (A3); also elsewhere on the board
MOSI_OUT: U27.11 (B3); also elsewhere on the board
RX_EXT: U29.5 (A4), U42.2 (A1); also elsewhere on the board
RX_OUT_PRIME: U29.10 (B4); also elsewhere on the board
RX_OUT_SEC: U42.13 (B1); also elsewhere on the board
SCK: U27.5 (A4); also elsewhere on the board
SCK_OUT: U27.10 (B4); also elsewhere on the board
SCL: U28.5 (SCL_A), U36.5 (SCL_A); also elsewhere on the board
SCL_OUT_PRIME: U28.8 (SCL_B); also elsewhere on the board
SCL_OUT_SEC: U36.8 (SCL_B); also elsewhere on the board
SDA_EXT: U28.4 (SDA_A), U36.4 (SDA_A); also elsewhere on the board
SDA_OUT_PRIME: U28.1 (SDA_B); also elsewhere on the board
SDA_OUT_SEC: U36.1 (SDA_B); also elsewhere on the board
TX_EXT: U29.4 (A3), U42.3 (A2); also elsewhere on the board
TX_OUT_PRIME: U29.11 (B3); also elsewhere on the board
TX_OUT_SEC: U42.12 (B2); also elsewhere on the board
VBUS_PRIME: U27.14 (VB), U28.7 (VCCCB), U29.14 (VB); also elsewhere on the board
VBUS_SEC: U36.7 (VCCCB), U42.14 (VB); also elsewhere on the board

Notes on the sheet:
Level Shifters: Port Side
I2C shifters, TCA9406
4-bit shifters, TXS0104
